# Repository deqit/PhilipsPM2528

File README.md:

# Reviving a Philips PM2528 Digital Multimeter
Picked up this vintage multimeter a while back. Half-functional, no manuals, and full of mystery. Perfect!

It’s built around an Intel 8035 microcontroller and packed with analog boards. There wasn’t a complete service manual anywhere, so I decided to dive in myself. This project's become a learning experience in hardware reverse engineering, firmware disassembly, and documentation.

Also see https://hackaday.io/project/203720-reviving-a-philips-pm2528-digital-multimeter

# The project
The goal of this project is fixing the multimeter. Well... maybe not really. In real life, the road towards that goal is much more interesting. And I'm documenting everything I found along the way.

In this repository you'll find:
- Original Philips-documentation (at least, what I could find, unfortunately in lo-res)
- Schematics (KiCad)
- PCB Layouts (KiCad)
- Schematic/PCB of a risercard, for testing the expansionboards
- Disassembled firmware, including annotations (Ghidra)
- A lot of documentation regarding relais-mapping, IO-expander-ports, etc.
- Detailed scope- and logic analyzer screenprints and capture-logs
- Deepdive: Explaination of how-everything-works
- etc.

Everything you find here is work-in-progress. It might be incomplete, and some parts may not be 100% accurate yet. If you spot something interesting or catch an error, feel free to drop me a message.

# The components
### Overview
- See [PM2528 Overview](/Deepdive/Overview/README.md "A very broad overview")
### Motherboard, display and firmware
- See [Motherboard (N1)](/Deepdive/N1/README.md "Motherboard (N1)")
- See [Display Unit (N2)](/Deepdive/N2/README.md "Display Unit (N2)")
- See [Firmware: memory, I/O and ports](/Deepdive/Firmware/README.md "Firmware: memory, I/O and ports")
### Risercard
- See [PM2528 Risercard](/Deepdive/Risercard/README.md "A Risercard for testing the Expansionboards")
### ADC
- See [ADC Overview](/Deepdive/ADC/README.md "The ADC in more detail")
- See [ADC Control (Expansionboard N20)](/Deepdive/N20/README.md "ADC Control (Expansionboard N20)")
- See [ADC Analog (Expansionboard N21)](/Deepdive/N21/README.md "ADC Analog (Expansionboard N21)")
### DC and resistance
- See [DC Amplifier (Expansionboard N22)](/Deepdive/N22/README.md "DC Amplifier (Expansionboard N22)")
- See [Current Source (Expansionboard N23)](/Deepdive/N23/README.md "Current Source (Expansionboard N23)")
### AC
- See [AC Amplifier (Expansionboard N24)](/Deepdive/N24/README.md "AC Amplifier (Expansionboard N24)")
- See [RMS Converter (Expansionboard N25)](/Deepdive/N25/README.md "RMS Converter (Expansionboard N25)")
- See [HF Unit (Expansionboard N26)](/Deepdive/N26/README.md "HF Unit (Expansionboard N26)")
- See [Peak Detector (Expansionboard N27)](/Deepdive/N27/README.md "Peak Detector (Expansionboard N27)")
### Outguard
- See [Galvanic Separation (Expansionboard N30)](/Deepdive/N30/README.md "Galvanic Separation (Expansionboard N30)")
- See [Analog Output (Expansionboard N31)](/Deepdive/N31/README.md "Analog Output (Expansionboard N31)")
- See [BCD Output (Expansionboard N34)](/Deepdive/N34/README.md "BCD Output (Expansionboard N34)")

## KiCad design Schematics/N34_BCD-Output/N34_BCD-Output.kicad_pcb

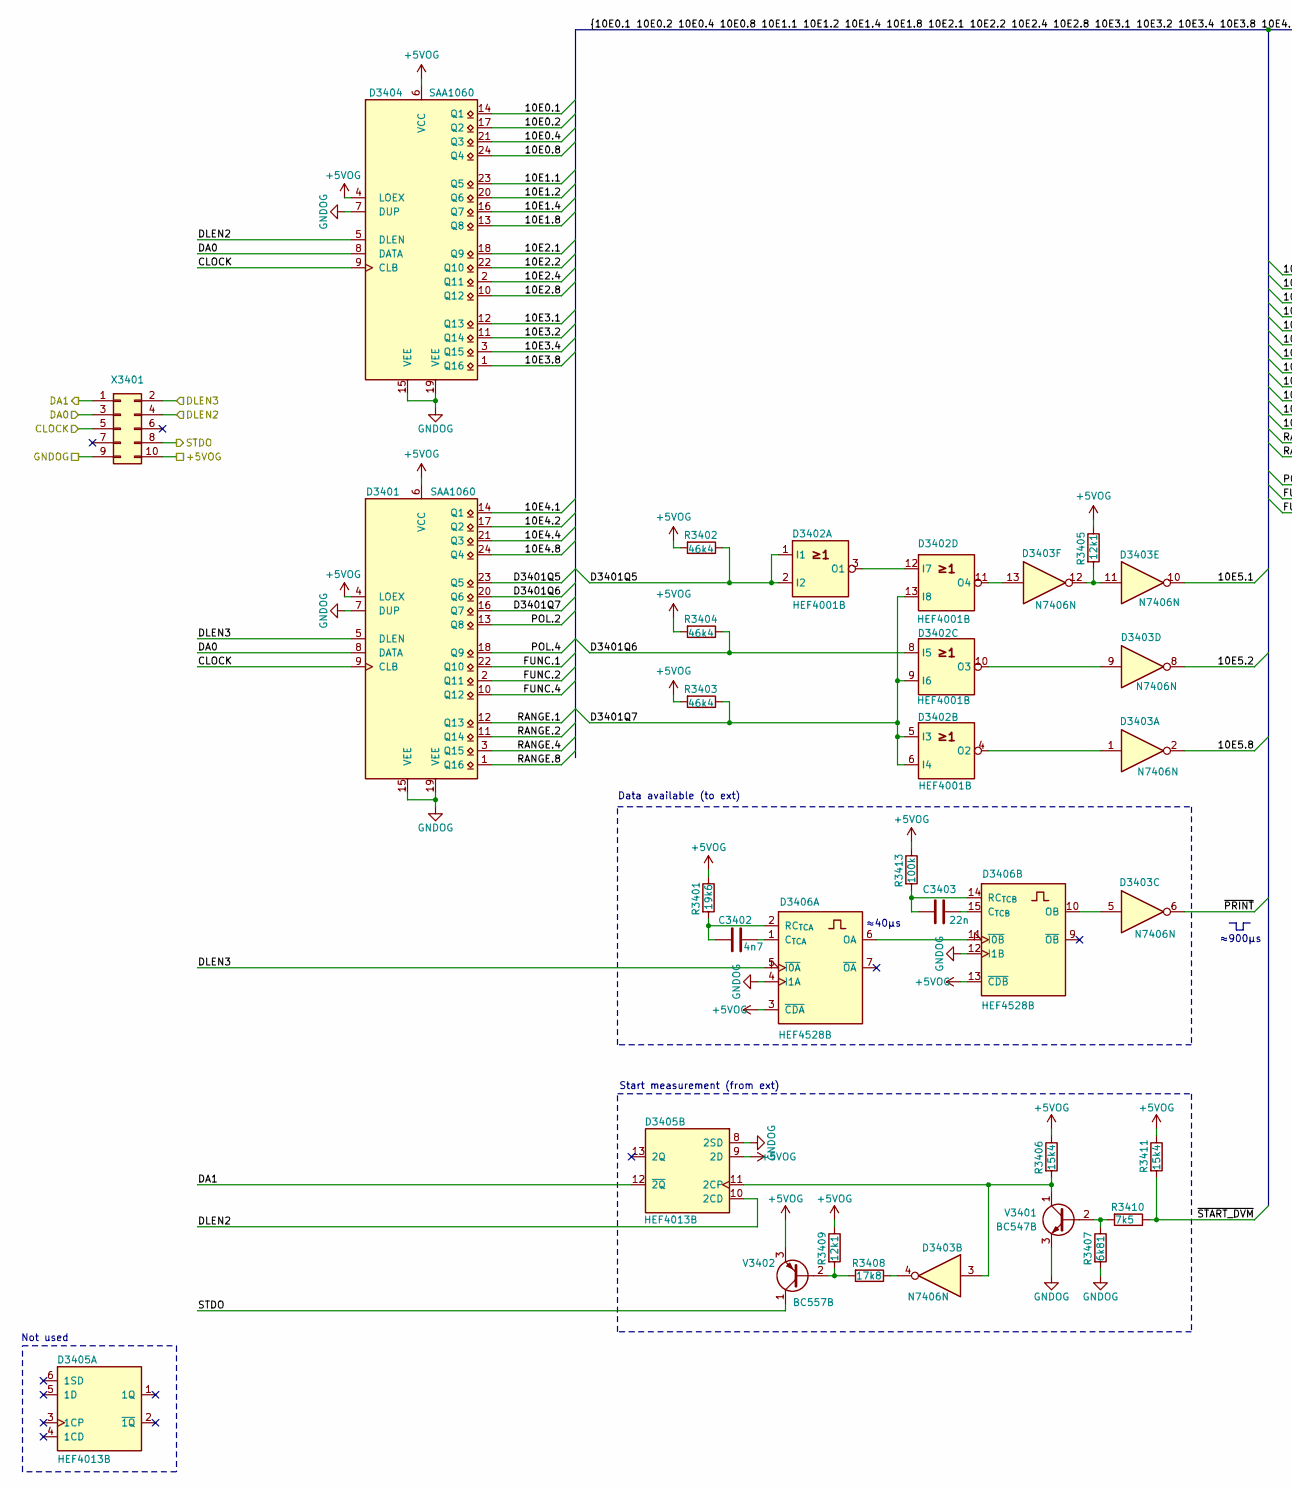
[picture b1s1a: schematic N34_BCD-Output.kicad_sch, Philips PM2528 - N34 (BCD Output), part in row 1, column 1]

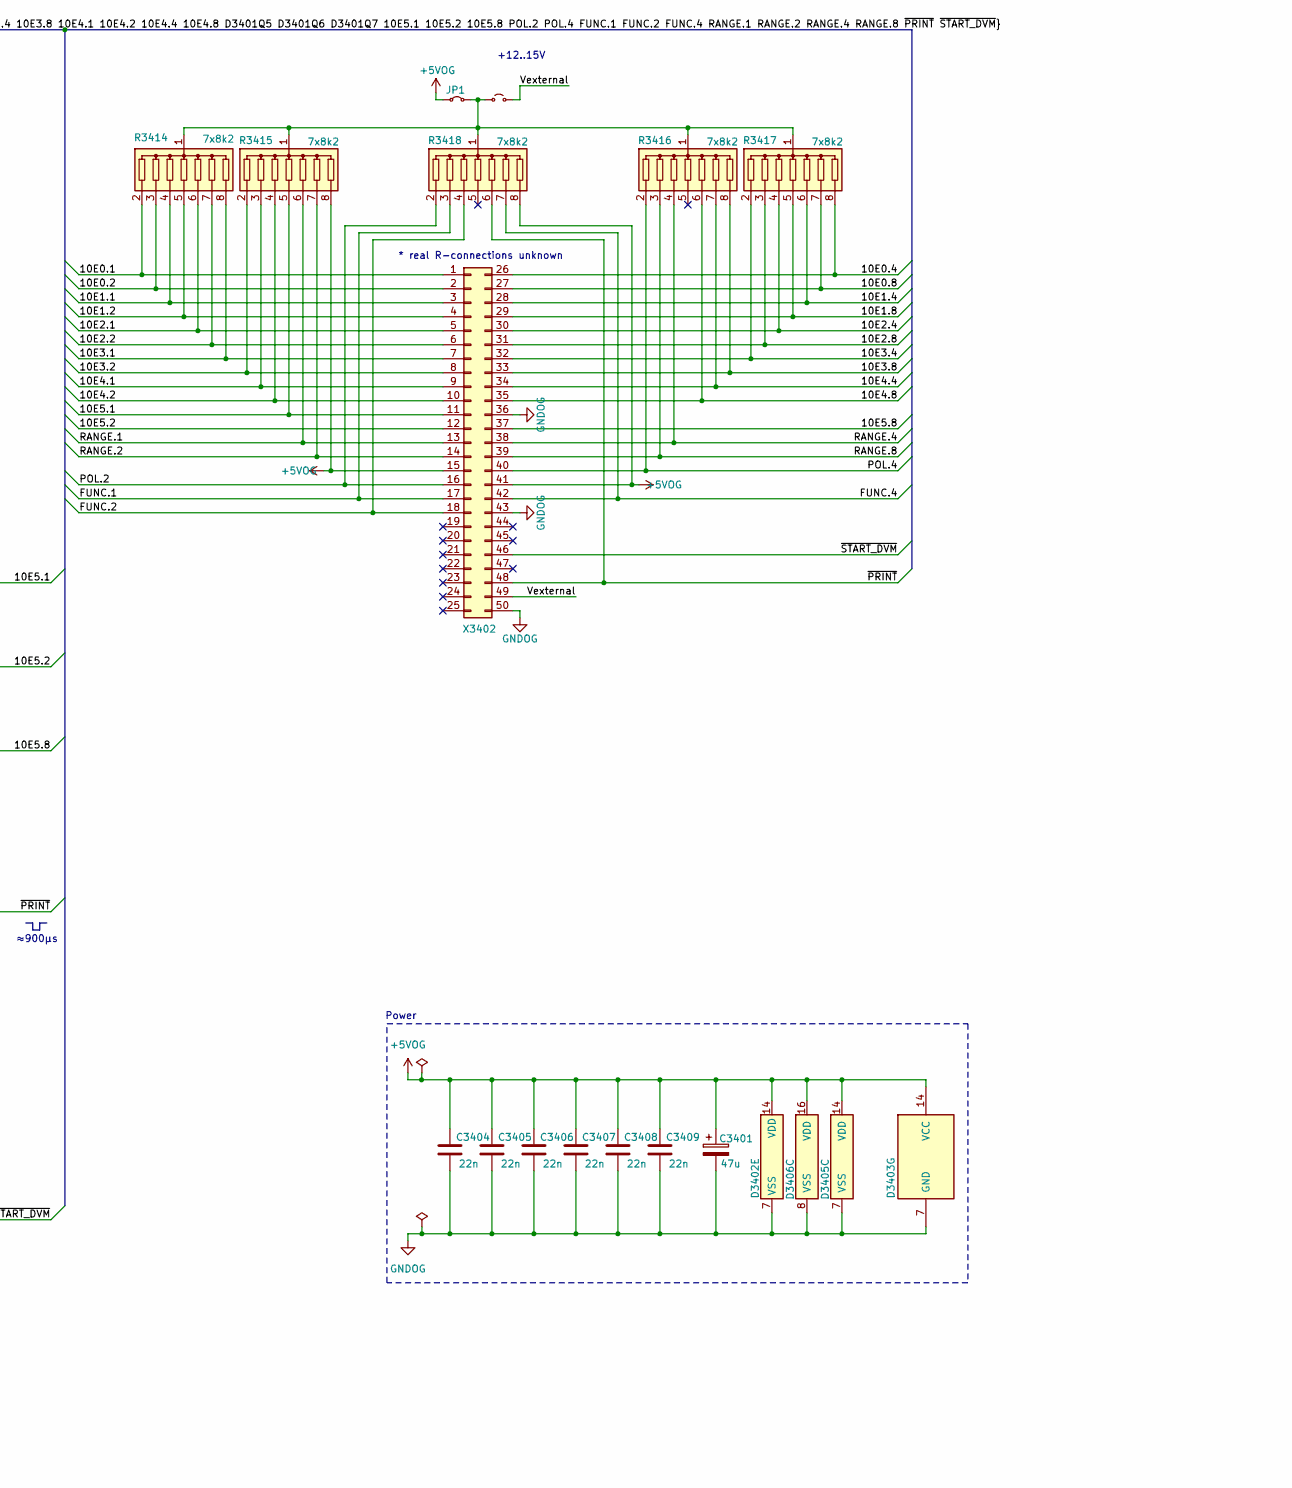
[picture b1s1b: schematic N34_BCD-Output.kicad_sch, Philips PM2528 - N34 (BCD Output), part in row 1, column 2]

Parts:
C3401: 47u; CP_Axial_L10.0mm_D6.0mm_P15.00mm_Horizontal
C3402: 4n7; C_Disc_D5.0mm_W2.5mm_P5.00mm
C3403, C3404, C3405, C3406, C3407, C3408, C3409: 22n; C_Disc_D5.0mm_W2.5mm_P5.00mm
D3401, D3404: SAA1060; DIP-24_W15.24mm
D3402: HEF4001B; DIP-14_W7.62mm
D3403: N7406N; DIP-14_W7.62mm
D3405: HEF4013B; DIP-14_W7.62mm
D3406: HEF4528B; DIP-16_W7.62mm
JP1: Jumper_2_Small_Bridged; TestPoint_Bridge_Pitch5.08mm_Drill0.7mm
JP2: Jumper_2_Small_Open; TestPoint_Bridge_Pitch5.08mm_Drill0.7mm
R3401: 19k6; R_Axial_DIN0207_L6.3mm_D2.5mm_P10.16mm_Horizontal
R3402, R3403, R3404: 46k4; R_Axial_DIN0207_L6.3mm_D2.5mm_P10.16mm_Horizontal
R3405, R3409: 12k1; R_Axial_DIN0207_L6.3mm_D2.5mm_P10.16mm_Horizontal
R3406, R3411: 15k4; R_Axial_DIN0207_L6.3mm_D2.5mm_P10.16mm_Horizontal
R3407: 6k81; R_Axial_DIN0207_L6.3mm_D2.5mm_P10.16mm_Horizontal
R3408: 17k8; R_Axial_DIN0207_L6.3mm_D2.5mm_P10.16mm_Horizontal
R3410: 7k5; R_Axial_DIN0207_L6.3mm_D2.5mm_P10.16mm_Horizontal
R3413: 100k; R_Axial_DIN0207_L6.3mm_D2.5mm_P10.16mm_Horizontal
R3414, R3415, R3416, R3417, R3418: 7x8k2; R_Array_SIP8
V3401: BC547B; TO-92_Inline
V3402: BC557B; TO-92_Inline
X3401: IDC-Header_2x05_P2.54mm_Vertical
X3402: BCD-connector; D-Shell_50_2x25_P2.16mm_Vertical

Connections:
+5VOG: C3401.1, C3404.1, C3405.1, C3406.1, C3407.1, C3408.1, C3409.1, D3401.4 (LOEX), D3401.6 (VCC), D3402.14 (VDD), D3403.14 (VCC), D3404.4 (LOEX), D3404.6 (VCC), D3405.9 (2D), D3405.14 (VDD), D3406.3 (~CDA), D3406.13 (~CDB), D3406.16 (VDD), JP1.2 (B), R3401.1, R3402.2, R3403.2, R3404.2, R3405.1, R3406.1, R3409.1, R3411.1, R3413.1, R3415.8 (R7), R3418.8 (R7), V3402.3 (E), X3401.10, X3402.15, X3402.41
/10E0.1: D3404.14 (Q1), R3414.2 (R1), X3402.1
/10E0.2: D3404.17 (Q2), R3414.3 (R2), X3402.2
/10E0.4: D3404.21 (Q3), R3417.8 (R7), X3402.26
/10E0.8: D3404.24 (Q4), R3417.7 (R6), X3402.27
/10E1.1: D3404.23 (Q5), R3414.4 (R3), X3402.3
/10E1.2: D3404.20 (Q6), R3414.5 (R4), X3402.4
/10E1.4: D3404.16 (Q7), R3417.6 (R5), X3402.28
/10E1.8: D3404.13 (Q8), R3417.5 (R4), X3402.29
/10E2.1: D3404.18 (Q9), R3414.6 (R5), X3402.5
/10E2.2: D3404.22 (Q10), R3414.7 (R6), X3402.6
/10E2.4: D3404.2 (Q11), R3417.4 (R3), X3402.30
/10E2.8: D3404.10 (Q12), R3417.3 (R2), X3402.31
/10E3.1: D3404.12 (Q13), R3414.8 (R7), X3402.7
/10E3.2: D3404.11 (Q14), R3415.2 (R1), X3402.8
/10E3.4: D3404.3 (Q15), R3417.2 (R1), X3402.32
/10E3.8: D3404.1 (Q16), R3416.8 (R7), X3402.33
/10E4.1: D3401.14 (Q1), R3415.3 (R2), X3402.9
/10E4.2: D3401.17 (Q2), R3415.4 (R3), X3402.10
/10E4.4: D3401.21 (Q3), R3416.7 (R6), X3402.34
/10E4.8: D3401.24 (Q4), R3416.6 (R5), X3402.35
/10E5.1: D3403.10, R3415.5 (R4), X3402.11
/10E5.2: D3403.8, X3402.12
/10E5.8: D3403.2, X3402.37
/CLOCK: D3401.9 (CLB), D3404.9 (CLB), X3401.5
/D3401Q5: D3401.23 (Q5), D3402.1 (I1), D3402.2 (I2), R3402.1
/D3401Q6: D3401.20 (Q6), D3402.8 (I5), R3404.1
/D3401Q7: D3401.16 (Q7), D3402.5 (I3), D3402.6 (I4), D3402.9 (I6), D3402.13 (I8), R3403.1
/DA0: D3401.8 (DATA), D3404.8 (DATA), X3401.3
/DA1: D3405.12 (~2Q), X3401.1
/DLEN2: D3404.5 (DLEN), D3405.10 (2CD), X3401.4
/DLEN3: D3401.5 (DLEN), D3406.5 (~I0A), X3401.2
/FUNC.1: D3401.22 (Q10), R3418.3 (R2), X3402.17
/FUNC.2: D3401.2 (Q11), R3418.4 (R3), X3402.18
/FUNC.4: D3401.10 (Q12), R3418.7 (R6), X3402.42
/POL.2: D3401.13 (Q8), R3418.2 (R1), X3402.16
/POL.4: D3401.18 (Q9), R3416.2 (R1), X3402.40
/RANGE.1: D3401.12 (Q13), R3415.6 (R5), X3402.13
/RANGE.2: D3401.11 (Q14), R3415.7 (R6), X3402.14
/RANGE.4: D3401.3 (Q15), R3416.4 (R3), X3402.38
/RANGE.8: D3401.1 (Q16), R3416.3 (R2), X3402.39
/STDO: V3402.1 (C), X3401.8
/Vexternal: JP2.2 (B), X3402.49
/~PRINT: D3403.6, R3418.6 (R5), X3402.48
/~START_DVM: R3410.1, R3411.2, X3402.46
GNDOG: C3401.2, C3404.2, C3405.2, C3406.2, C3407.2, C3408.2, C3409.2, D3401.7 (DUP), D3401.15 (VEE), D3401.19 (VEE), D3402.7 (VSS), D3403.7 (GND), D3404.7 (DUP), D3404.15 (VEE), D3404.19 (VEE), D3405.7 (VSS), D3405.8 (2SD), D3406.4 (I1A), D3406.8 (VSS), D3406.12 (I1B), R3407.2, V3401.3 (E), X3401.9, X3402.36, X3402.43, X3402.50
unnamed: D3402.3 (O1), D3402.12 (I7)
unnamed: D3402.4 (O2), D3403.1
unnamed: D3402.10 (O3), D3403.9
unnamed: D3402.11 (O4), D3403.13
unnamed: D3403.4, R3408.1
unnamed: D3403.11, D3403.12, R3405.2
unnamed: D3403.3, D3405.11 (2CP), R3406.2, V3401.1 (C)
unnamed: C3402.2, D3406.1 (C_{TCA})
unnamed: D3406.6 (OA), D3406.11 (~I0B)
unnamed: C3402.1, D3406.2 (RC_{TCA}), R3401.2
unnamed: C3403.2, D3406.15 (C_{TCB})
unnamed: D3403.5, D3406.10 (OB)
unnamed: C3403.1, D3406.14 (RC_{TCB}), R3413.2
unnamed: JP1.1 (A_1), JP2.1 (A_1), R3414.1 (COM), R3415.1 (COM), R3416.1 (COM), R3417.1 (COM), R3418.1 (COM)
unnamed: R3407.1, R3410.2, V3401.2 (B)
unnamed: R3408.2, R3409.2, V3402.2 (B)

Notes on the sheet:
Data available (to ext)
* real R-connections unknown
+12..15V
Start measurement (from ext)
≈900µs
Not used
Power
≈40µs

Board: 2 copper layers, 38 parts (0 on the bottom side), 61 nets, no tracks yet.

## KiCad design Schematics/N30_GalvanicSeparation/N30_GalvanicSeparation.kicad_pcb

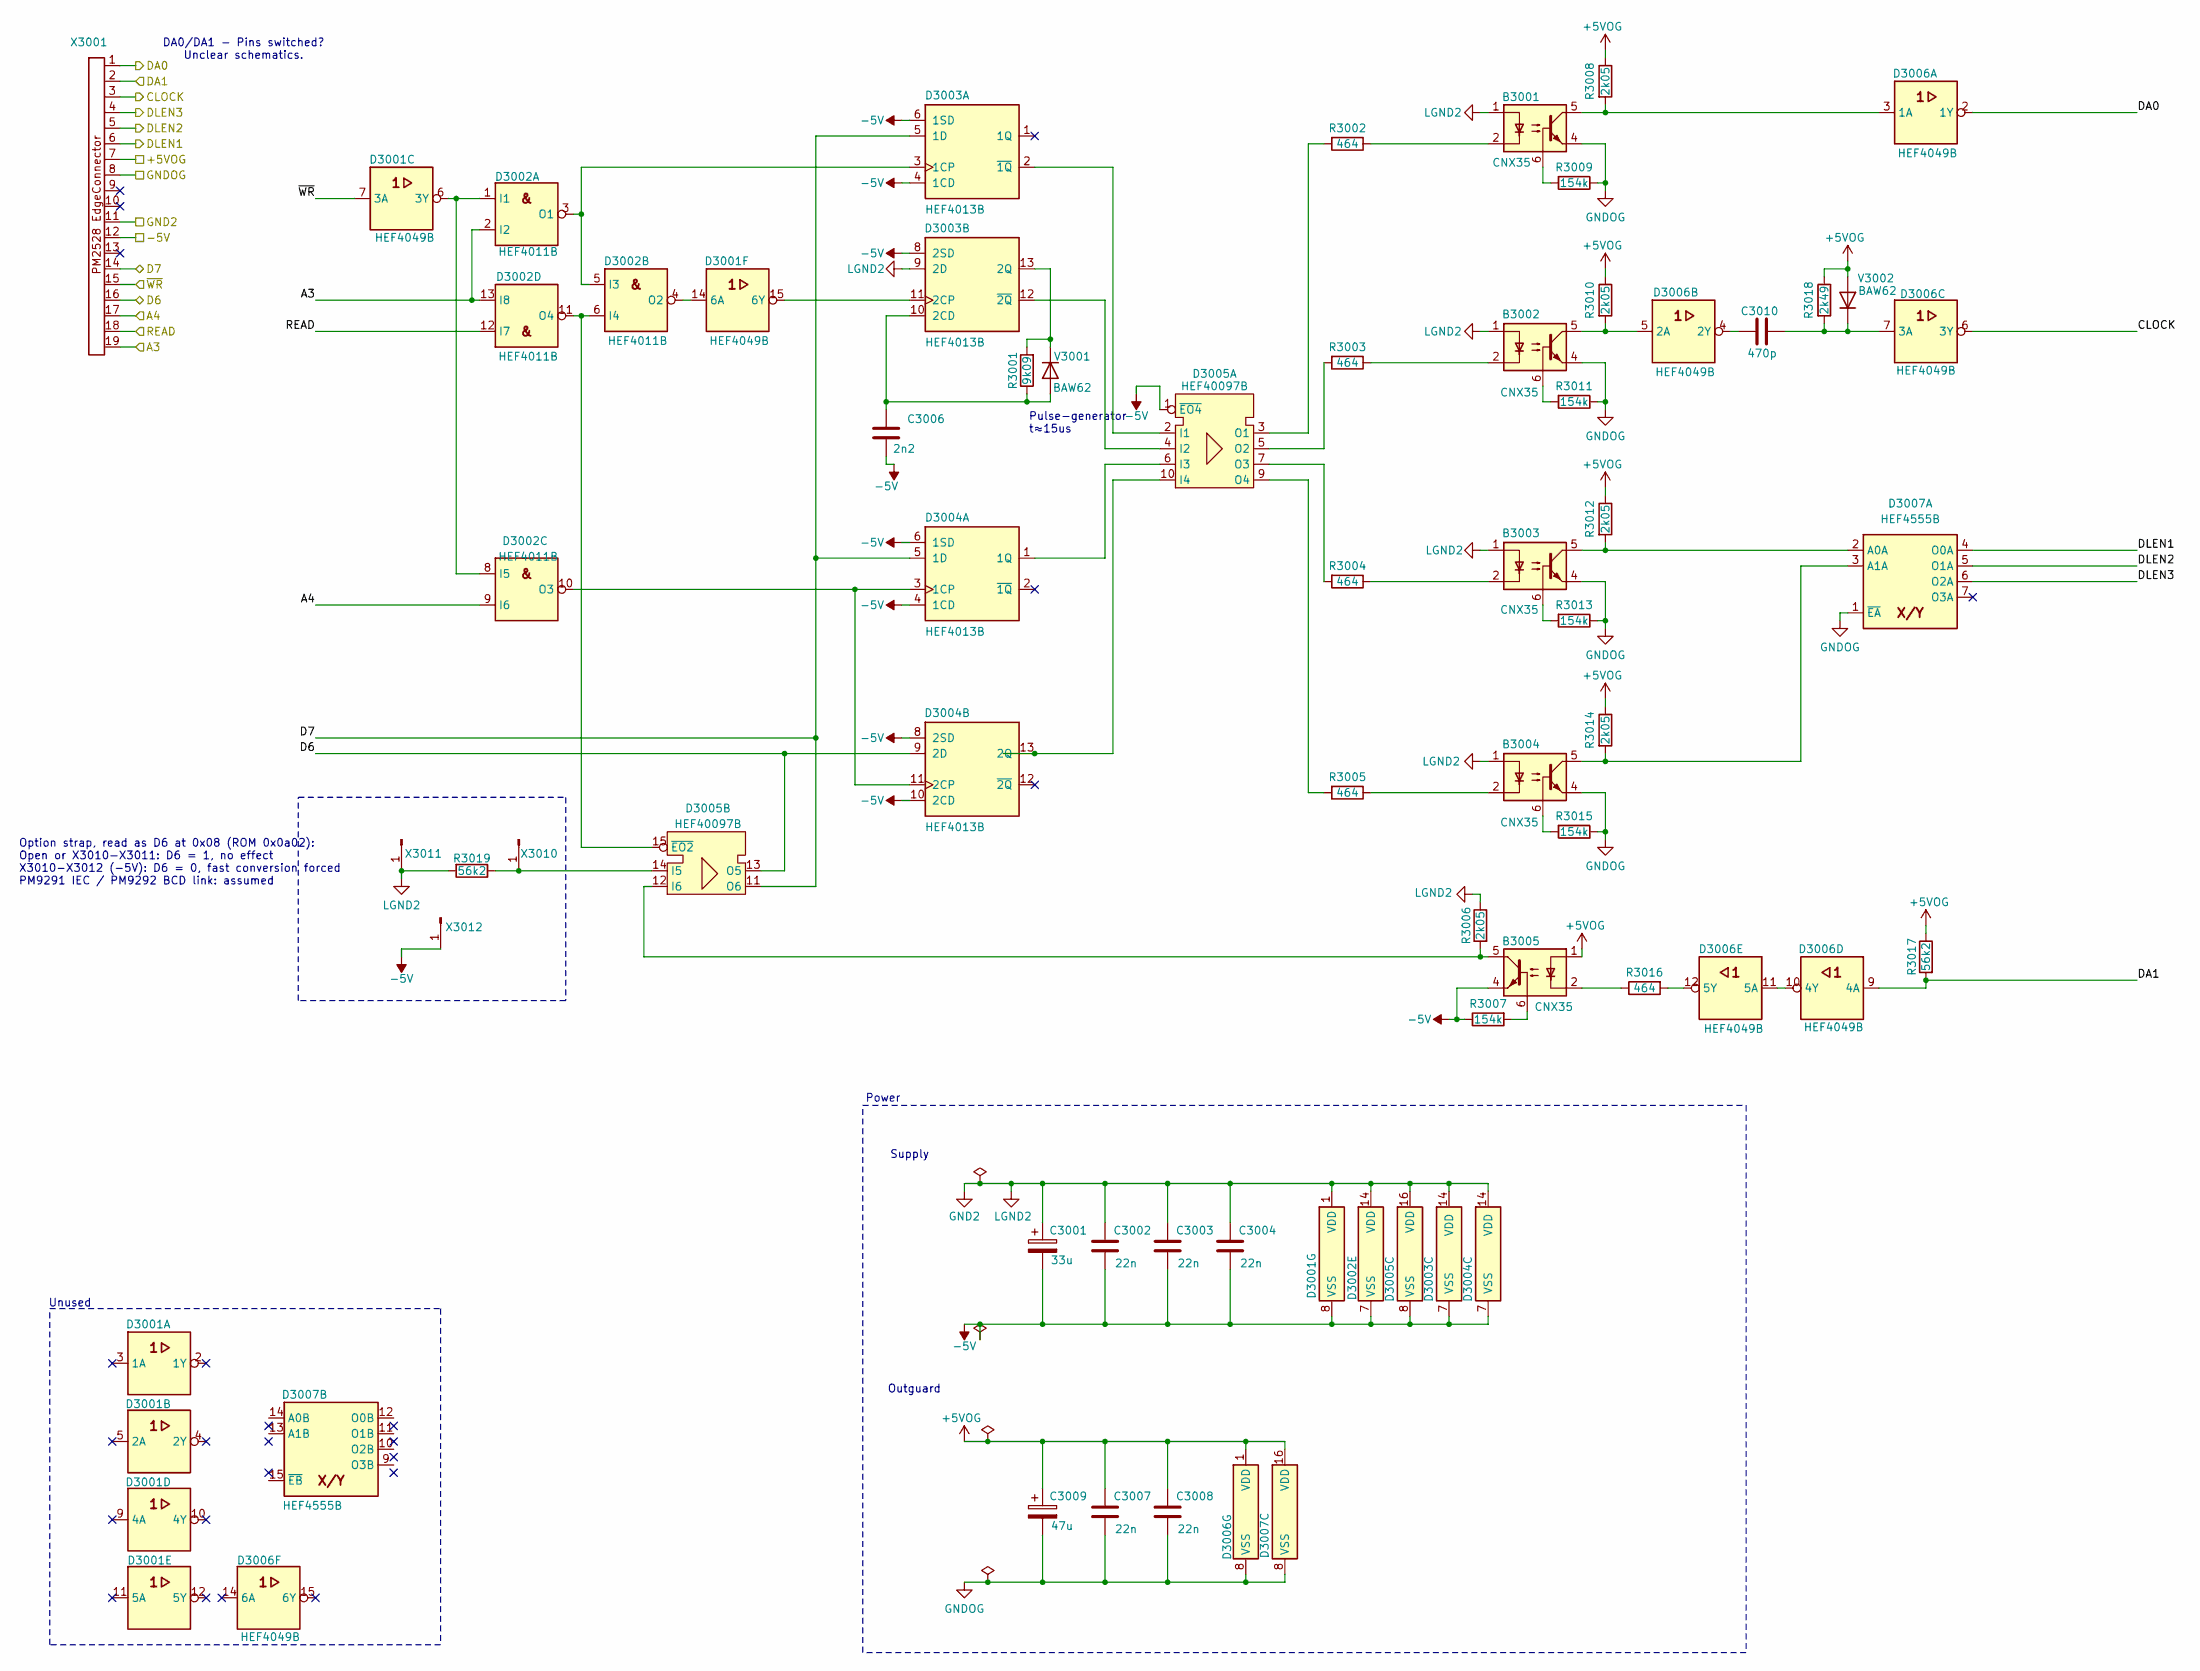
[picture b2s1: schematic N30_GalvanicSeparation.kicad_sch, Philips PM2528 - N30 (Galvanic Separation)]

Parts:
B3001, B3002, B3003, B3004, B3005: CNX35; CNX35_DIP-6_W7.62mm
C3001: 33u; CP_Radial_Tantal_D7.0mm_P5.00mm
C3002, C3003, C3004, C3007, C3008: 22n; C_Axial_L5.1mm_D3.1mm_P10.00mm_Horizontal
C3006: 2n2; C_Axial_L5.1mm_D3.1mm_P10.00mm_Horizontal
C3009: 47u; CP_Axial_L10.0mm_D6.0mm_P15.00mm_Horizontal
C3010: 470p; C_Axial_L5.1mm_D3.1mm_P10.00mm_Horizontal
D3001, D3006: HEF4049B; DIP-16_W7.62mm
D3002: HEF4011B; DIP-14_W7.62mm
D3003, D3004: HEF4013B; DIP-14_W7.62mm
D3005: HEF40097B; DIP-16_W7.62mm
D3007: HEF4555B; DIP-16_W7.62mm
R3001: 9k09; R_Axial_DIN0207_L6.3mm_D2.5mm_P10.16mm_Horizontal
R3002, R3003, R3004, R3005, R3016: 464; R_Axial_DIN0207_L6.3mm_D2.5mm_P10.16mm_Horizontal
R3006, R3008, R3010, R3012, R3014: 2k05; R_Axial_DIN0207_L6.3mm_D2.5mm_P10.16mm_Horizontal
R3007, R3009, R3011, R3013, R3015: 154k; R_Axial_DIN0207_L6.3mm_D2.5mm_P10.16mm_Horizontal
R3017, R3019: 56k2; R_Axial_DIN0207_L6.3mm_D2.5mm_P10.16mm_Horizontal
R3018: 2k49; R_Axial_DIN0207_L6.3mm_D2.5mm_P10.16mm_Horizontal
V3001, V3002: BAW62; D_DO-35_SOD27_P10.16mm_Horizontal
X3001: PM2528Edgeconnector
X3010, X3011, X3012: Conn_01x01_MountingPin; Pin_D1.1mm_L8.5mm_W2.5mm_FlatFork

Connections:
+5VOG: B3005.1 (A), C3007.1, C3008.1, C3009.1, D3006.1 (VDD), D3007.16 (VDD), R3008.1, R3010.1, R3012.1, R3014.1, R3017.1, R3018.1, V3002.2 (A), X3001.7
-5V: B3005.4 (E), C3001.2, C3002.2, C3003.2, C3004.2, C3006.2, D3001.8 (VSS), D3002.7 (VSS), D3003.4 (1CD), D3003.6 (1SD), D3003.7 (VSS), D3003.8 (2SD), D3004.4 (1CD), D3004.6 (1SD), D3004.7 (VSS), D3004.8 (2SD), D3004.10 (2CD), D3005.1 (~EO4), D3005.8 (VSS), R3007.1, X3001.12, X3012.1
/A3: D3002.2 (I2), D3002.13 (I8), X3001.19
/A4: D3002.9 (I6), X3001.17
/CLOCK: D3006.6 (3Y), X3001.3
/D6: D3004.9 (2D), D3005.13 (O5), X3001.16
/D7: D3003.5 (1D), D3004.5 (1D), D3005.11 (O6), X3001.14
/DA0: D3006.2 (1Y), X3001.1
/DA1: D3006.9 (4A), R3017.2, X3001.2
/DLEN1: D3007.4 (O0A), X3001.6
/DLEN2: D3007.5 (O1A), X3001.5
/DLEN3: D3007.6 (O2A), X3001.4
/READ: D3002.12 (I7), X3001.18
/~WR: D3001.7 (3A), X3001.15
GND2: B3001.1 (A), B3002.1 (A), B3003.1 (A), B3004.1 (A), C3001.1, C3002.1, C3003.1, C3004.1, D3001.1 (VDD), D3002.14 (VDD), D3003.9 (2D), D3003.14 (VDD), D3004.14 (VDD), D3005.16 (VDD), R3006.1, R3019.2, X3001.11, X3011.1
GNDOG: B3001.4 (E), B3002.4 (E), B3003.4 (E), B3004.4 (E), C3007.2, C3008.2, C3009.2, D3006.8 (VSS), D3007.1 (~EA), D3007.8 (VSS), R3009.1, R3011.1, R3013.1, R3015.1, X3001.8
unnamed: B3001.6 (B), R3009.2
unnamed: B3001.5 (C), D3006.3 (1A), R3008.2
unnamed: B3001.2 (K), R3002.1
unnamed: B3002.6 (B), R3011.2
unnamed: B3002.5 (C), D3006.5 (2A), R3010.2
unnamed: B3002.2 (K), R3003.1
unnamed: B3003.6 (B), R3013.2
unnamed: B3003.5 (C), D3007.2 (A0A), R3012.2
unnamed: B3003.2 (K), R3004.1
unnamed: B3004.6 (B), R3015.2
unnamed: B3004.5 (C), D3007.3 (A1A), R3014.2
unnamed: B3004.2 (K), R3005.1
unnamed: B3005.6 (B), R3007.2
unnamed: B3005.5 (C), D3005.12 (I6), R3006.2
unnamed: B3005.2 (K), R3016.1
unnamed: D3001.6 (3Y), D3002.1 (I1), D3002.8 (I5)
unnamed: D3001.14 (6A), D3002.4 (O2)
unnamed: D3001.15 (6Y), D3003.11 (2CP)
unnamed: D3002.3 (O1), D3002.5 (I3), D3003.3 (1CP)
unnamed: D3002.6 (I4), D3002.11 (O4), D3005.15 (~EO2)
unnamed: D3002.10 (O3), D3004.3 (1CP), D3004.11 (2CP)
unnamed: D3003.2 (~1Q), D3005.2 (I1)
unnamed: C3006.1, D3003.10 (2CD), R3001.1, V3001.2 (A)
unnamed: D3003.13 (2Q), R3001.2, V3001.1 (K)
unnamed: D3003.12 (~2Q), D3005.4 (I2)
unnamed: D3004.1 (1Q), D3005.6 (I3)
unnamed: D3004.13 (2Q), D3005.10 (I4)
unnamed: D3005.3 (O1), R3002.2
unnamed: D3005.5 (O2), R3003.2
unnamed: D3005.7 (O3), R3004.2
unnamed: D3005.9 (O4), R3005.2
unnamed: D3005.14 (I5), R3019.1, X3010.1
unnamed: C3010.1, D3006.4 (2Y)
unnamed: C3010.2, D3006.7 (3A), R3018.2, V3002.1 (K)
unnamed: D3006.10 (4Y), D3006.11 (5A)
unnamed: D3006.12 (5Y), R3016.2

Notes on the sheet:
Unused
Outguard
Supply
Pulse-generator t≈15us
Option strap, read as D6 at 0x08 (ROM 0x0a02): Open or X3010-X3011: D6 = 1, no effect X3010-X3012 (-5V): D6 = 0, fast conversion forced PM9291 IEC / PM9292 BCD link: assumed
DA0/DA1 - Pins switched? Unclear schematics.
Power

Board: 2 copper layers, 42 parts (0 on the bottom side), 52 nets, no tracks yet.

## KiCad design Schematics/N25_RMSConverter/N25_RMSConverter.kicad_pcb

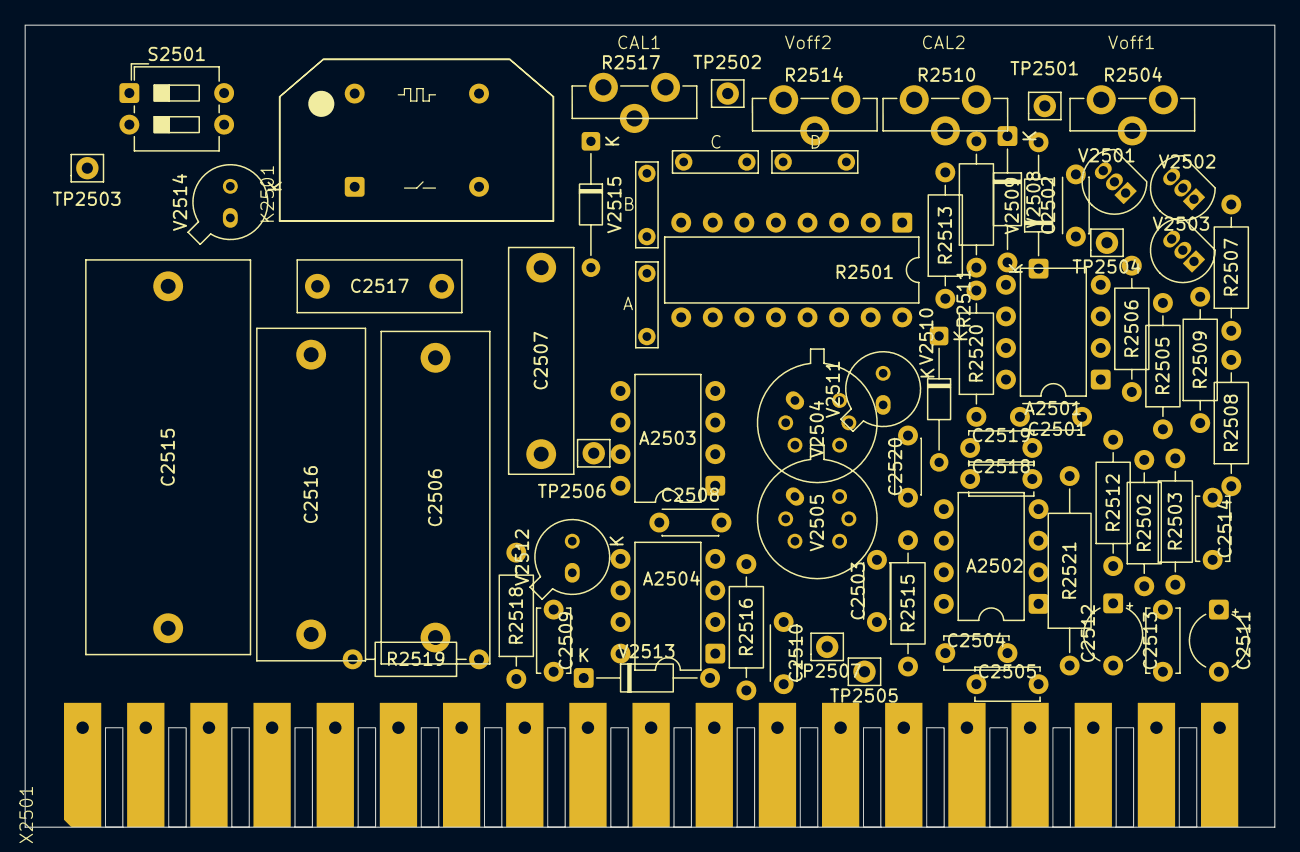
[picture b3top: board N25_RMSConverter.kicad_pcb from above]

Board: 2 copper layers, 100.5 x 64.5 mm, 72 parts (0 on the bottom side), 49 nets, no tracks yet.

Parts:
A2501, A2503, A2504: LM308AN; DIP-8_W7.62mm
A2502: LF356BN; DIP-8_W7.62mm
C2501: 22p; C_Disc_D4.3mm_W1.9mm_P5.00mm
C2502, C2510: 470p; C_Disc_D4.3mm_W1.9mm_P5.00mm
C2503: 100p; C_Disc_D4.3mm_W1.9mm_P5.00mm
C2504, C2505, C2518: 10n; C_Disc_D5.0mm_W2.5mm_P5.00mm
C2506: 3u3; C_Rect_L26.5mm_W8.5mm_P22.50mm_MKS4
C2507: 330n; C_Rect_L18.0mm_W5.0mm_P15.00mm_FKS3_FKP3
C2508: 10p; C_Disc_D4.3mm_W1.9mm_P5.00mm
C2509: 100p; C_Disc_D5.0mm_W2.5mm_P5.00mm
C2511, C2512: 6u8; CP_Radial_Tantal_D4.5mm_P5.00mm
C2513, C2514: 22n; C_Disc_D5.0mm_W2.5mm_P5.00mm
C2515: 6u8; C_Rect_L31.5mm_W13.0mm_P27.50mm_MKS4
C2516: 2u2; C_Rect_L26.5mm_W8.5mm_P22.50mm_MKS4
C2517: 100n; C_Rect_L13.0mm_W4.0mm_P10.00mm_FKS3_FKP3_MKS4
C2519: 2n2; C_Disc_D5.0mm_W2.5mm_P5.00mm
C2520: 18p; C_Disc_D4.3mm_W1.9mm_P5.00mm
JP2501: A; TestPoint_Bridge_Pitch5.08mm_Drill0.7mm
JP2502: B; TestPoint_Bridge_Pitch5.08mm_Drill0.7mm
JP2503: C; TestPoint_Bridge_Pitch5.08mm_Drill0.7mm
JP2504: D; TestPoint_Bridge_Pitch5.08mm_Drill0.7mm
K2501: Reed relay assy
R2501: OM529; DIP-16_W7.62mm
R2502: 19R6; R_Axial_DIN0207_L6.3mm_D2.5mm_P10.16mm_Horizontal
R2503, R2513: 301k; R_Axial_DIN0207_L6.3mm_D2.5mm_P10.16mm_Horizontal
R2504, R2514: 47k; Trimmer vertical
R2505: 750; R_Axial_DIN0207_L6.3mm_D2.5mm_P10.16mm_Horizontal
R2506: 590; R_Axial_DIN0207_L6.3mm_D2.5mm_P10.16mm_Horizontal
R2507: 301; R_Axial_DIN0207_L6.3mm_D2.5mm_P10.16mm_Horizontal
R2508: 7k87; R_Axial_DIN0207_L6.3mm_D2.5mm_P10.16mm_Horizontal
R2509: 1k96; R_Axial_DIN0207_L6.3mm_D2.5mm_P10.16mm_Horizontal
R2510: 1K; Trimmer vertical
R2511: 8R25; R_Axial_DIN0207_L6.3mm_D2.5mm_P10.16mm_Horizontal
R2512: 115; R_Axial_DIN0207_L6.3mm_D2.5mm_P10.16mm_Horizontal
R2515, R2518: 2k05; R_Axial_DIN0207_L6.3mm_D2.5mm_P10.16mm_Horizontal
R2516: 4k02; R_Axial_DIN0207_L6.3mm_D2.5mm_P10.16mm_Horizontal
R2517: 330; Trimmer vertical
R2519: 3k01; R_Axial_DIN0207_L6.3mm_D2.5mm_P10.16mm_Horizontal
R2520: 5M6; R_Axial_DIN0207_L6.3mm_D2.5mm_P10.16mm_Horizontal
R2521: 33M; R_Axial_DIN0309_L9.0mm_D3.2mm_P15.24mm_Horizontal
S2501: SW_DPST_x2; SW_DIP_SPSTx02_Slide_6.7x6.64mm_W7.62mm_P2.54mm_LowProfile
TP2501, TP2502, TP2504, TP2507: Pin_D0.9mm_L10.0mm_W2.4mm_FlatFork
TP2503: OUT; Pin_D0.9mm_L10.0mm_W2.4mm_FlatFork
TP2505: IN; Pin_D0.9mm_L10.0mm_W2.4mm_FlatFork
TP2506: 0V; Pin_D0.9mm_L10.0mm_W2.4mm_FlatFork
V2501, V2502: BC547B; TO-92_Inline
V2503: BC559B; TO-92_Inline
V2504, V2505: MAT01GH; MAT01_TO-78-6
V2508, V2509, V2513: BAW62; D_DO-35_SOD27_P10.16mm_Horizontal
V2510: BZX79-B4V7; D_DO-34_SOD68_P10.16mm_Horizontal
V2511, V2512, V2514: BAV45; BAV45_TO-18-2
V2515: BAX12A; D_DO-34_SOD68_P10.16mm_Horizontal
X2501: PM2528Edgeconnector

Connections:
+5V: R2518.2, X2501.5
+15V: A2501.7 (V+), A2502.7 (V+), A2503.7 (V+), A2504.7 (V+), C2504.1, C2511.1, C2513.1, R2504.1, R2505.2, R2506.2, R2514.1, X2501.4
-15V: A2501.4 (V-), A2502.4 (V-), A2503.4 (V-), A2504.4 (V-), C2505.2, C2512.2, C2514.2, R2504.3, R2507.1, R2509.1, R2514.3, V2510.2 (A), X2501.3
/IN: C2518.2, R2501.16, R2521.1, TP2505.1 (1_1), X2501.7
/N25_REL2501: K2501.10, V2515.2 (A), X2501.15
/OUT: C2516.2, C2517.2, R2501.10, TP2503.1 (1_1), V2514.2 (A), X2501.13
GND1: A2503.3 (+), A2504.3 (+), C2509.2, C2517.1, K2501.5, R2502.1, R2512.1, S2501.3 (A), TP2506.1 (1_1), V2504.2 (B1), V2504.5 (B2), X2501.8, X2501.11, X2501.12
GND2: C2504.2, C2505.1, C2511.2, C2512.1, C2513.2, C2514.1, K2501.6, R2508.1, R2519.1, V2515.1 (K), X2501.1, X2501.14
unnamed: A2501.3 (+), R2502.2, R2503.2
unnamed: A2501.2 (-), C2502.2, R2510.2, TP2501.1 (1_1)
unnamed: A2501.1 (CompenA), C2501.2
unnamed: A2501.8 (CompenB), C2501.1
unnamed: A2502.3 (+), R2512.2, R2513.2
unnamed: A2502.2 (-), C2519.2, C2520.1, R2501.15, V2504.1 (C1), V2511.1 (K)
unnamed: A2503.2 (-), C2506.1, C2507.1, R2501.13, V2505.6 (C2)
unnamed: A2503.1 (CompenA), C2508.2
unnamed: A2503.8 (CompenB), C2508.1
unnamed: A2504.2 (-), C2510.2, R2517.1, R2517.2, V2504.6 (C2), V2512.1 (K)
unnamed: A2504.8 (CompenB), C2509.1
unnamed: C2515.2, R2501.11
unnamed: C2518.1, R2520.2
unnamed: C2519.1, R2521.2
unnamed: JP2501.1 (A_1), R2501.8, R2517.3
unnamed: JP2502.1 (A_1), R2501.7
unnamed: JP2503.1 (A_1), R2501.6
unnamed: JP2504.1 (A_1), R2501.5
unnamed: K2501.1, R2501.9
unnamed: R2501.1, R2510.3, R2511.1, R2520.1
unnamed: R2501.3, R2510.1, R2511.2
unnamed: R2503.1, R2504.2
unnamed: R2513.1, R2514.2
unnamed: C2506.2, S2501.1 (A)
unnamed: A2503.6, C2507.2, R2501.12, S2501.2 (B), TP2502.1 (1_1)
unnamed: C2515.1, C2516.1, S2501.4 (B)
unnamed: A2501.6, V2501.2 (B), V2510.1 (K)
unnamed: R2505.1, V2501.1 (C), V2503.2 (B)
unnamed: R2507.2, V2501.3 (E), V2502.3 (E)
unnamed: C2502.1, R2508.2, R2509.2, V2502.2 (B)
unnamed: V2502.1 (C), V2503.1 (C), V2508.2 (A), V2509.1 (K)
unnamed: R2506.1, V2503.3 (E)
unnamed: V2504.3 (E1), V2505.1 (C1), V2505.2 (B1)
unnamed: V2504.4 (E2), V2505.5 (B2), V2513.2 (A)
unnamed: C2503.2, R2515.2, TP2507.1 (1_1), V2505.3 (E1), V2505.4 (E2)
unnamed: R2501.14, TP2504.1 (1_1), V2508.1 (K)
unnamed: R2501.2, V2509.2 (A)
unnamed: A2502.6, C2503.1, C2520.2, R2515.1, V2511.2 (A)
unnamed: A2504.6, C2510.1, R2516.2, V2512.2 (A)
unnamed: R2516.1, V2513.1 (K)
unnamed: R2518.1, R2519.2, V2514.1 (K)
